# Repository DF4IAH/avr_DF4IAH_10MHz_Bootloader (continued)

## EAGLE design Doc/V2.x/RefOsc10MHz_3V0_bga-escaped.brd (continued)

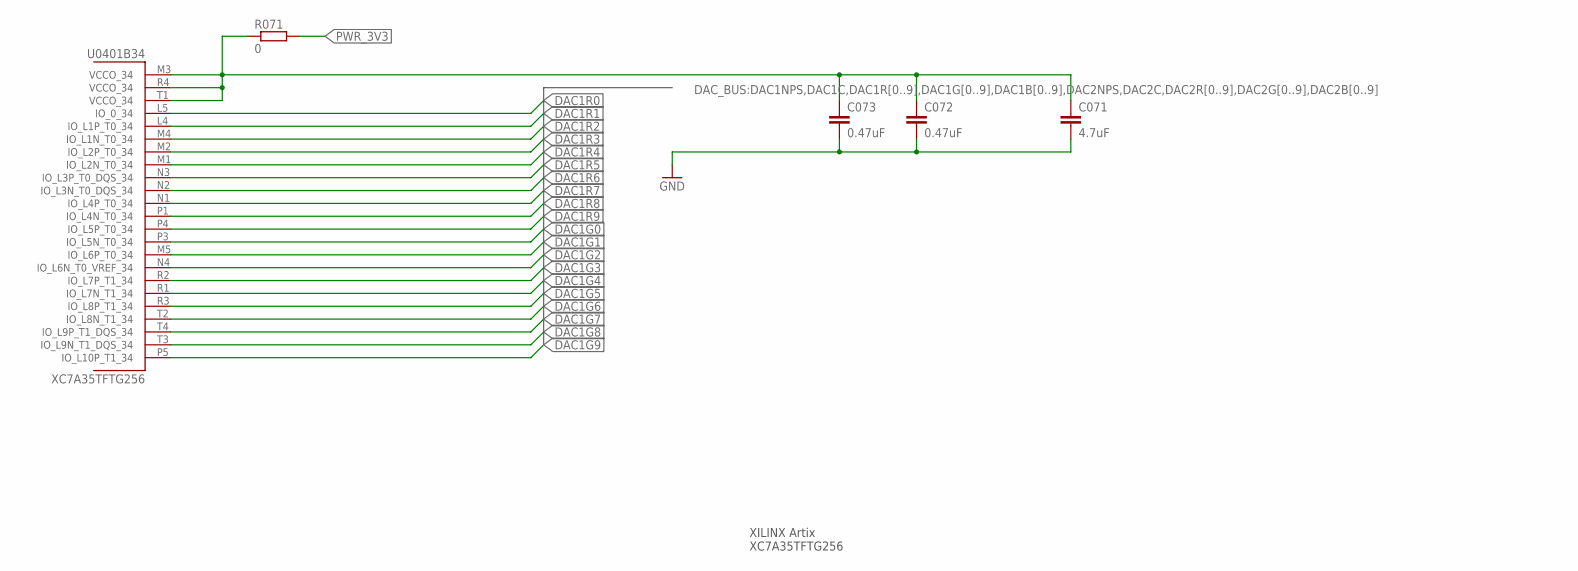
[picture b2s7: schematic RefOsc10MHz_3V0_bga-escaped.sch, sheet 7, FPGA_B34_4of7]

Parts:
C071: 4.7uF; C0402
C072, C073: 0.47uF; C0402
R071: 0; R0402
U0401: XC7A35TFTG256; FTG256_0MM4

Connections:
DAC1G0: U0401.P3 (IO_L5N_T0_34)
DAC1G1: U0401.M5 (IO_L6P_T0_34)
DAC1G2: U0401.N4 (IO_L6N_T0_VREF_34)
DAC1G3: U0401.R2 (IO_L7P_T1_34)
DAC1G4: U0401.R1 (IO_L7N_T1_34)
DAC1G5: U0401.R3 (IO_L8P_T1_34)
DAC1G6: U0401.T2 (IO_L8N_T1_34)
DAC1G7: U0401.T4 (IO_L9P_T1_DQS_34)
DAC1G8: U0401.T3 (IO_L9N_T1_DQS_34)
DAC1G9: U0401.P5 (IO_L10P_T1_34)
DAC1R0: U0401.L5 (IO_0_34)
DAC1R1: U0401.L4 (IO_L1P_T0_34)
DAC1R2: U0401.M4 (IO_L1N_T0_34)
DAC1R3: U0401.M2 (IO_L2P_T0_34)
DAC1R4: U0401.M1 (IO_L2N_T0_34)
DAC1R5: U0401.N3 (IO_L3P_T0_DQS_34)
DAC1R6: U0401.N2 (IO_L3N_T0_DQS_34)
DAC1R7: U0401.N1 (IO_L4P_T0_34)
DAC1R8: U0401.P1 (IO_L4N_T0_34)
DAC1R9: U0401.P4 (IO_L5P_T0_34)
FPGA_VCCO_34: C071.1, C072.1, C073.1, R071.1, U0401.M3 (VCCO_34), U0401.R4 (VCCO_34), U0401.T1 (VCCO_34)
GND: C071.2, C072.2, C073.2; also elsewhere on the board
PWR_3V3: R071.2; also elsewhere on the board

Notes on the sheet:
XILINX Artix XC7A35TFTG256

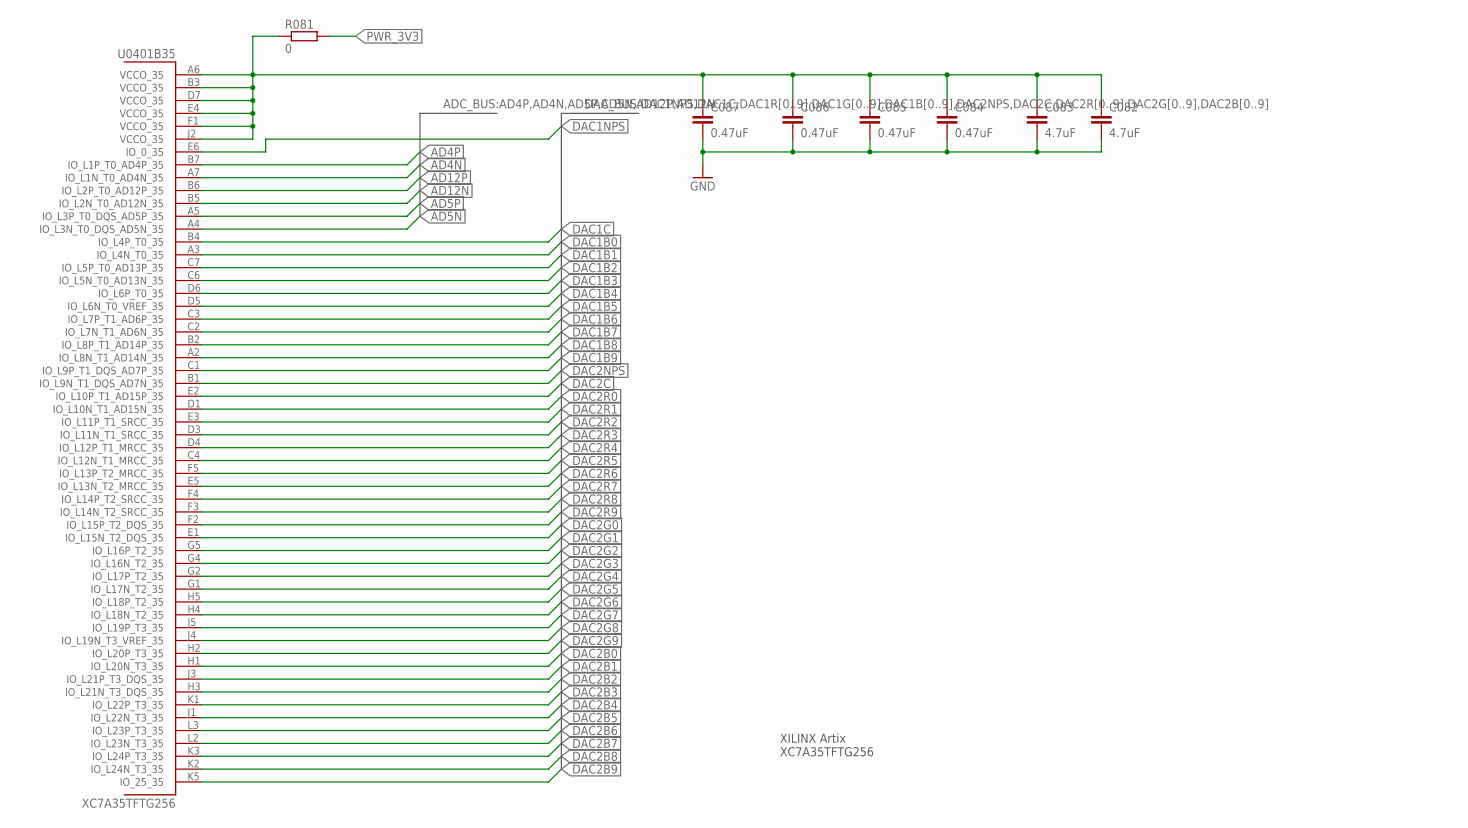
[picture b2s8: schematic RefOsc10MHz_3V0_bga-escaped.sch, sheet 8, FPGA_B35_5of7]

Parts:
C082, C083: 4.7uF; C0402
C084, C085, C086, C087: 0.47uF; C0402
R081: 0; R0402
U0401: XC7A35TFTG256; FTG256_0MM4

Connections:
AD4N: U0401.A7 (IO_L1N_T0_AD4N_35)
AD4P: U0401.B7 (IO_L1P_T0_AD4P_35)
AD5N: U0401.A4 (IO_L3N_T0_DQS_AD5N_35)
AD5P: U0401.A5 (IO_L3P_T0_DQS_AD5P_35)
AD12N: U0401.B5 (IO_L2N_T0_AD12N_35)
AD12P: U0401.B6 (IO_L2P_T0_AD12P_35)
DAC1B0: U0401.A3 (IO_L4N_T0_35)
DAC1B1: U0401.C7 (IO_L5P_T0_AD13P_35)
DAC1B2: U0401.C6 (IO_L5N_T0_AD13N_35)
DAC1B3: U0401.D6 (IO_L6P_T0_35)
DAC1B4: U0401.D5 (IO_L6N_T0_VREF_35)
DAC1B5: U0401.C3 (IO_L7P_T1_AD6P_35)
DAC1B6: U0401.C2 (IO_L7N_T1_AD6N_35)
DAC1B7: U0401.B2 (IO_L8P_T1_AD14P_35)
DAC1B8: U0401.A2 (IO_L8N_T1_AD14N_35)
DAC1B9: U0401.C1 (IO_L9P_T1_DQS_AD7P_35)
DAC1C: U0401.B4 (IO_L4P_T0_35)
DAC1NPS: U0401.E6 (IO_0_35)
DAC2B0: U0401.H1 (IO_L20N_T3_35)
DAC2B1: U0401.J3 (IO_L21P_T3_DQS_35)
DAC2B2: U0401.H3 (IO_L21N_T3_DQS_35)
DAC2B3: U0401.K1 (IO_L22P_T3_35)
DAC2B4: U0401.J1 (IO_L22N_T3_35)
DAC2B5: U0401.L3 (IO_L23P_T3_35)
DAC2B6: U0401.L2 (IO_L23N_T3_35)
DAC2B7: U0401.K3 (IO_L24P_T3_35)
DAC2B8: U0401.K2 (IO_L24N_T3_35)
DAC2B9: U0401.K5 (IO_25_35)
DAC2C: U0401.E2 (IO_L10P_T1_AD15P_35)
DAC2G0: U0401.E1 (IO_L15N_T2_DQS_35)
DAC2G1: U0401.G5 (IO_L16P_T2_35)
DAC2G2: U0401.G4 (IO_L16N_T2_35)
DAC2G3: U0401.G2 (IO_L17P_T2_35)
DAC2G4: U0401.G1 (IO_L17N_T2_35)
DAC2G5: U0401.H5 (IO_L18P_T2_35)
DAC2G6: U0401.H4 (IO_L18N_T2_35)
DAC2G7: U0401.J5 (IO_L19P_T3_35)
DAC2G8: U0401.J4 (IO_L19N_T3_VREF_35)
DAC2G9: U0401.H2 (IO_L20P_T3_35)
DAC2NPS: U0401.B1 (IO_L9N_T1_DQS_AD7N_35)
DAC2R0: U0401.D1 (IO_L10N_T1_AD15N_35)
DAC2R1: U0401.E3 (IO_L11P_T1_SRCC_35)
DAC2R2: U0401.D3 (IO_L11N_T1_SRCC_35)
DAC2R3: U0401.D4 (IO_L12P_T1_MRCC_35)
DAC2R4: U0401.C4 (IO_L12N_T1_MRCC_35)
DAC2R5: U0401.F5 (IO_L13P_T2_MRCC_35)
DAC2R6: U0401.E5 (IO_L13N_T2_MRCC_35)
DAC2R7: U0401.F4 (IO_L14P_T2_SRCC_35)
DAC2R8: U0401.F3 (IO_L14N_T2_SRCC_35)
DAC2R9: U0401.F2 (IO_L15P_T2_DQS_35)
FPGA_VCCO_35: C082.1, C083.1, C084.1, C085.1, C086.1, C087.1, R081.1, U0401.A6 (VCCO_35), U0401.B3 (VCCO_35), U0401.D7 (VCCO_35), U0401.E4 (VCCO_35), U0401.F1 (VCCO_35), U0401.J2 (VCCO_35)
GND: C082.2, C083.2, C084.2, C085.2, C086.2, C087.2; also elsewhere on the board
PWR_3V3: R081.2; also elsewhere on the board

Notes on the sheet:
XILINX Artix XC7A35TFTG256

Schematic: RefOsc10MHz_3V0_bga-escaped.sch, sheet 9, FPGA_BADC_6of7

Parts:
C091: 4.7uF; C0402
C092: 0.47uF; C0402
R091: 0; R0402
U0401: XC7A35TFTG256; FTG256_0MM4

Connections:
AGND: U0401.G7 (GNDADC_0), U0401.H7 (VREFN_0), U0401.J7 (VN_0); also elsewhere on the board
FPGA_ADC_VP_0: U0401.H8 (VP_0)
FPGA_VCCADC_0: C091.1, C092.1, R091.1, U0401.G8 (VCCADC_0)
GND: C091.2, C092.2; also elsewhere on the board
PWR_1V25_PREC: U0401.J8 (VREFP_0)
PWR_VCCADC: R091.2; also elsewhere on the board

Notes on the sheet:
XILINX Artix XC7A35TFTG256

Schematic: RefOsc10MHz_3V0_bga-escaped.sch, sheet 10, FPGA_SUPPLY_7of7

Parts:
C1001: 100uF; C1206
C1002, C1003, C1022, C1023: 4.7uF; C0402
C1004, C1005, C1006, C1012, C1024, C1025, C1026: 0.47uF; C0402
C1011, C1021: 47uF; C0805
R101, R102, R103, R104, R105: 0; R0402
U0401: XC7A35TFTG256; FTG256_0MM4

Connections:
FPGA_DXN_0: R105.1, U0401.K7 (DXN_0)
FPGA_DXP_0: R104.1, U0401.K8 (DXP_0)
FPGA_VCCAUX: C1021.1, C1022.1, C1023.1, C1024.1, C1025.1, C1026.1, R103.1, U0401.G10 (VCCAUX), U0401.J10 (VCCAUX), U0401.K11 (VCCAUX), U0401.L10 (VCCAUX)
FPGA_VCCBRAM: C1011.1, C1012.1, R102.1, U0401.E10 (VCCBRAM), U0401.F11 (VCCBRAM)
FPGA_VCCINT: C1001.1, C1002.1, C1003.1, C1004.1, C1005.1, C1006.1, R101.1, U0401.F7 (VCCINT), U0401.F9 (VCCINT), U0401.G6 (VCCINT), U0401.H9 (VCCINT), U0401.J6 (VCCINT), U0401.K9 (VCCINT), U0401.L8 (VCCINT)
GND: C1001.2, C1002.2, C1003.2, C1004.2, C1005.2, C1006.2, C1011.2, C1012.2, C1021.2, C1022.2, C1023.2, C1024.2, C1025.2, C1026.2, R104.2, R105.2, U0401.A1 (GND), U0401.A11 (GND), U0401.B8 (GND), U0401.C5 (GND), U0401.C15 (GND), U0401.D2 (GND), U0401.D12 (GND), U0401.E9 (GND), U0401.F6 (GND), U0401.F10 (GND), U0401.F16 (GND), U0401.G3 (GND), U0401.G9 (GND), U0401.G13 (GND), U0401.H6 (GND), U0401.J9 (GND), U0401.J11 (GND), U0401.K4 (GND), U0401.K6 (GND), U0401.K14 (GND), U0401.L1 (GND), U0401.L11 (GND), U0401.M8 (GND), U0401.N5 (GND), U0401.N15 (GND), U0401.P2 (GND), U0401.P12 (GND), U0401.R9 (GND), U0401.T6 (GND), U0401.T16 (GND); also elsewhere on the board
PWR_1V0: R101.2, R102.2; also elsewhere on the board
PWR_1V8: R103.2; also elsewhere on the board

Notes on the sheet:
XILINX Artix XC7A35TFTG256

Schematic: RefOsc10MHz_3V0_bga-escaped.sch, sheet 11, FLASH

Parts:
R111: 4.7k; R0805
R112, R113: 100k; R0805
U111: N25Q128A13ESE40F; SOP2-8

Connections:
FPGA_SPI_CCLK: U111.6 (C); also elsewhere on the board
FPGA_SPI_D00_MOSI: U111.5 (DQ0); also elsewhere on the board
FPGA_SPI_D01_DIN: U111.2 (DQ1); also elsewhere on the board
FPGA_SPI_D02: R112.1, U111.3 (W#_VPP_DQ2); also elsewhere on the board
FPGA_SPI_D03: R113.1, U111.7 (HOLD#/DQ3); also elsewhere on the board
FPGA_SPI_FCS_B#: R111.1, U111.1 (S#); also elsewhere on the board
GND: U111.4 (VSS); also elsewhere on the board
PWR_3V3: R111.2, R112.2, R113.2, U111.8 (VDD); also elsewhere on the board

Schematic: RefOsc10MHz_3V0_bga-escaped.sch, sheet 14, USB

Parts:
C141: 47uF; C0805
C142: 100n; C0805
CON141: TYCO-AMP_USBUSB-B_SMT; TYCO-AMP_USB-B_SMT
D141, D142: BZX84-C3V6; TO236
R141, R142: 68; R0805
R143: 1M; R0805
R144: 1.5k; R0805
RP141: 1206L025YR_0.5A; M1206

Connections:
GND: C141.2, C142.2, CON141.4 (GND), D141.A, D142.A, R143.1; also elsewhere on the board
PWR_5V0: C141.1, C142.1, RP141.2; also elsewhere on the board
USB_DISC: R144.2; also elsewhere on the board
USB_D_MIN1: CON141.2 (D-), D142.C, R142.1, R144.1
USB_D_MNS: R142.2; also elsewhere on the board
USB_D_PLS: R141.2; also elsewhere on the board
USB_D_PLS1: CON141.3 (D+), D141.C, R141.1, R143.2
USB_PWR1: CON141.1 (VBUS), RP141.1

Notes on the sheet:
USB-B

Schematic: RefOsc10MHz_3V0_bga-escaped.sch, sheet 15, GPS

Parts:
C151: 100n; C0805
CON151: HEADER-2X5SMD; 2X5SMD
LP151: WE-CBF_300R; L3216C
R151, R152: 100k; R0805
RP151: 1206L012WR_0.1A; M1206
U151: TJ1513MTBD

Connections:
GND: C151.2, CON151.1, CON151.9, CON151.10, U151.6 (GND), U151.17 (GND), U151.20 (GND), U151.22 (GND); also elsewhere on the board
GPS_ANT: LP151.1, U151.21 (RF_IN); also elsewhere on the board
GPS_NMEA_RX: CON151.5, R152.1, U151.5 (RXD1); also elsewhere on the board
GPS_NMEA_TX: CON151.6, U151.4 (TXD1); also elsewhere on the board
GPS_PPS: CON151.7, U151.3 (TIMEPULSE); also elsewhere on the board
GPS_PWR_3V3: C151.1, CON151.4, R151.2, R152.2, RP151.2, U151.13 (VCC)
GPS_RESET: R151.1, U151.11 (RESET); also elsewhere on the board
unnamed: LP151.2, U151.19 (VCC_RF)
PWR_3V3: RP151.1; also elsewhere on the board
PWR_5V0: CON151.3; also elsewhere on the board
PWR_BACKUP_3V3: CON151.2, U151.12 (V_BAKP); also elsewhere on the board

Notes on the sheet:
GPS - PINs: 1 GND 2 V_BAT, Memory Supply, Goldcap 3 VCC 5V 4 V_ANT 5V, fused 5 GPS NMEA RX 6 GPS NMEA TX 7 PPS (1 Hz) 8 Ref. 10 kHz 9 GND 10 GND

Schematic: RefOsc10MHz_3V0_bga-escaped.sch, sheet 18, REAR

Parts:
CON181, CON183, CON184, CON185, CON186: MCX-J-P-X-RA-SM1
CON182: SD-73100-0105; MOLEX_BNC-JACK-50R_SD-73100-0105
R181: 51; R0805
R182, R183: 120; R0805
U181: OPA357; SOT-23-6

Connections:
GND: CON181.2, CON181.3, CON181.4, CON181.5, CON182.2, CON182.3, CON183.2, CON183.3, CON183.4, CON183.5, CON184.2, CON184.3, CON184.4, CON184.5, CON185.2, CON185.3, CON185.4, CON185.5, CON186.2, CON186.3, CON186.4, CON186.5, R182.1, R183.1, U181.2 (V-); also elsewhere on the board
GPS_ANT: CON181.1; also elsewhere on the board
unnamed: R181.1, U181.1 (OUT)
unnamed: CON182.1, R181.2
PWR_5V0: U181.6 (V+); also elsewhere on the board
REFC_10MHZ_EN: U181.5 (ENABLE); also elsewhere on the board
REFC_10MHZ_N: R183.2, U181.4 (-IN); also elsewhere on the board
REFC_10MHZ_P: R182.2, U181.3 (+IN); also elsewhere on the board
SIG_CH0_I: CON183.1
SIG_CH0_Q: CON184.1
SIG_CH1_I: CON185.1
SIG_CH1_Q: CON186.1

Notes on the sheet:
10 MHz RefClk Out
GPS Ant In
CH0 I Out
CH0 Q Out
CH1 I Out
CH1 Q Out

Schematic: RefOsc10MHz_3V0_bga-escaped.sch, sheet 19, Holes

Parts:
H191, H192, H193, H194: MOUNT-PAD-ROUND2.8; 2,8-PAD

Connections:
GND: H191.B2,8, H192.B2,8, H193.B2,8, H194.B2,8; also elsewhere on the board

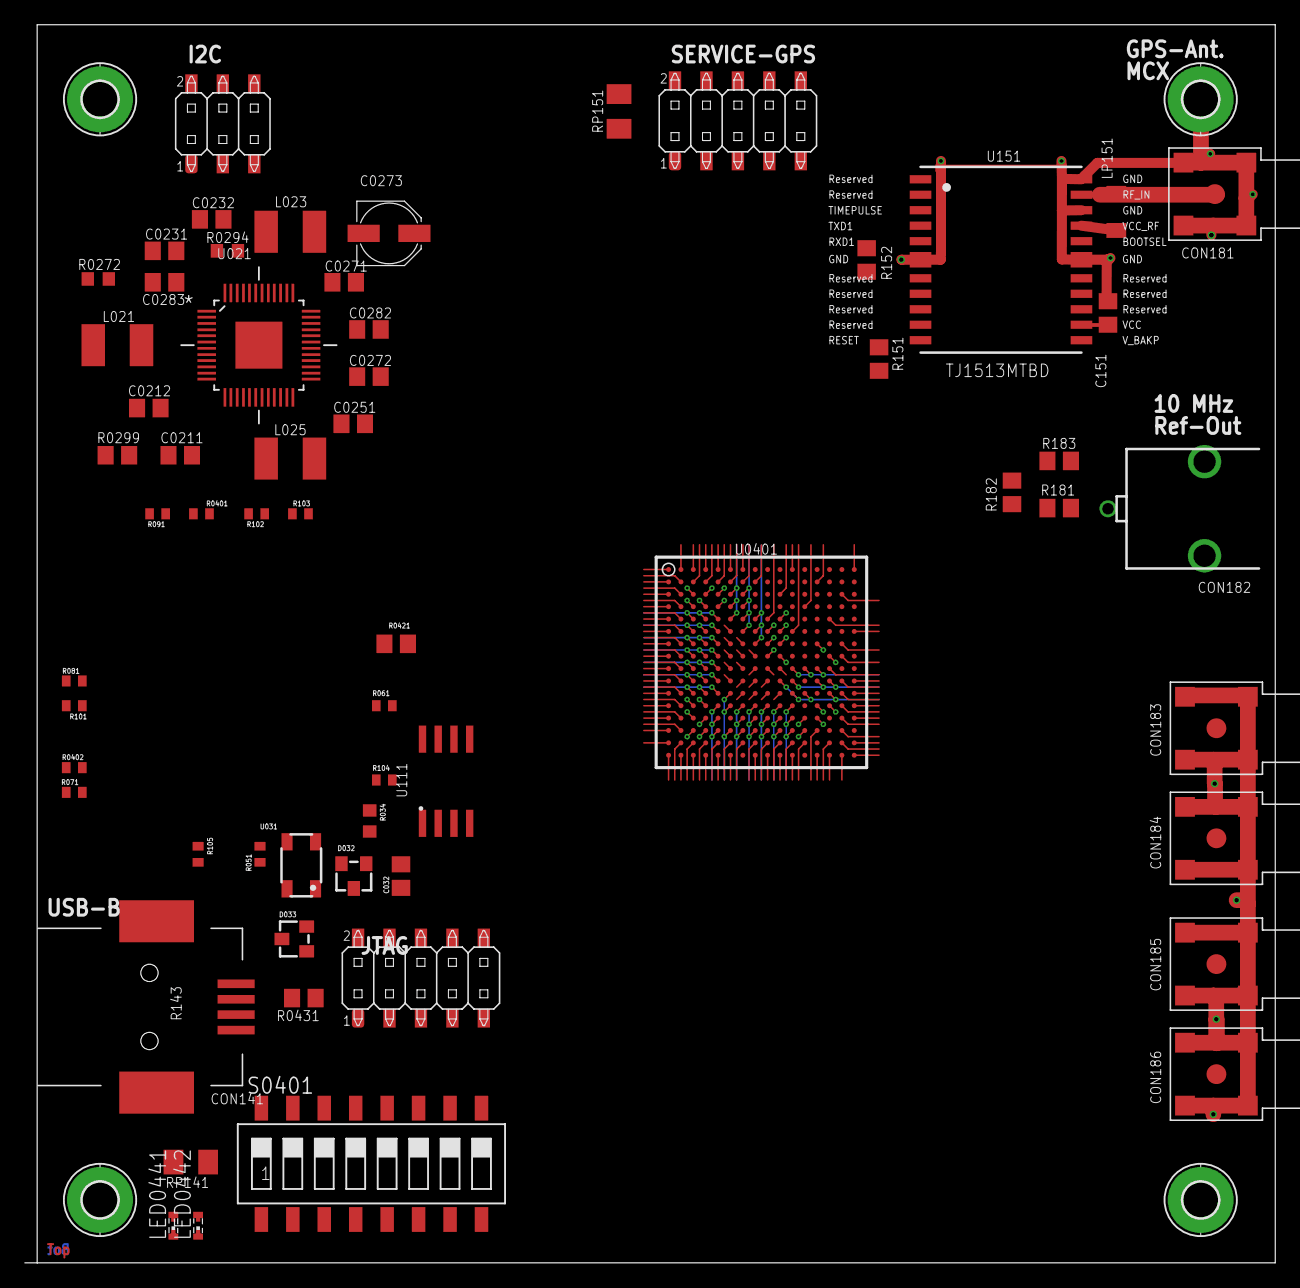
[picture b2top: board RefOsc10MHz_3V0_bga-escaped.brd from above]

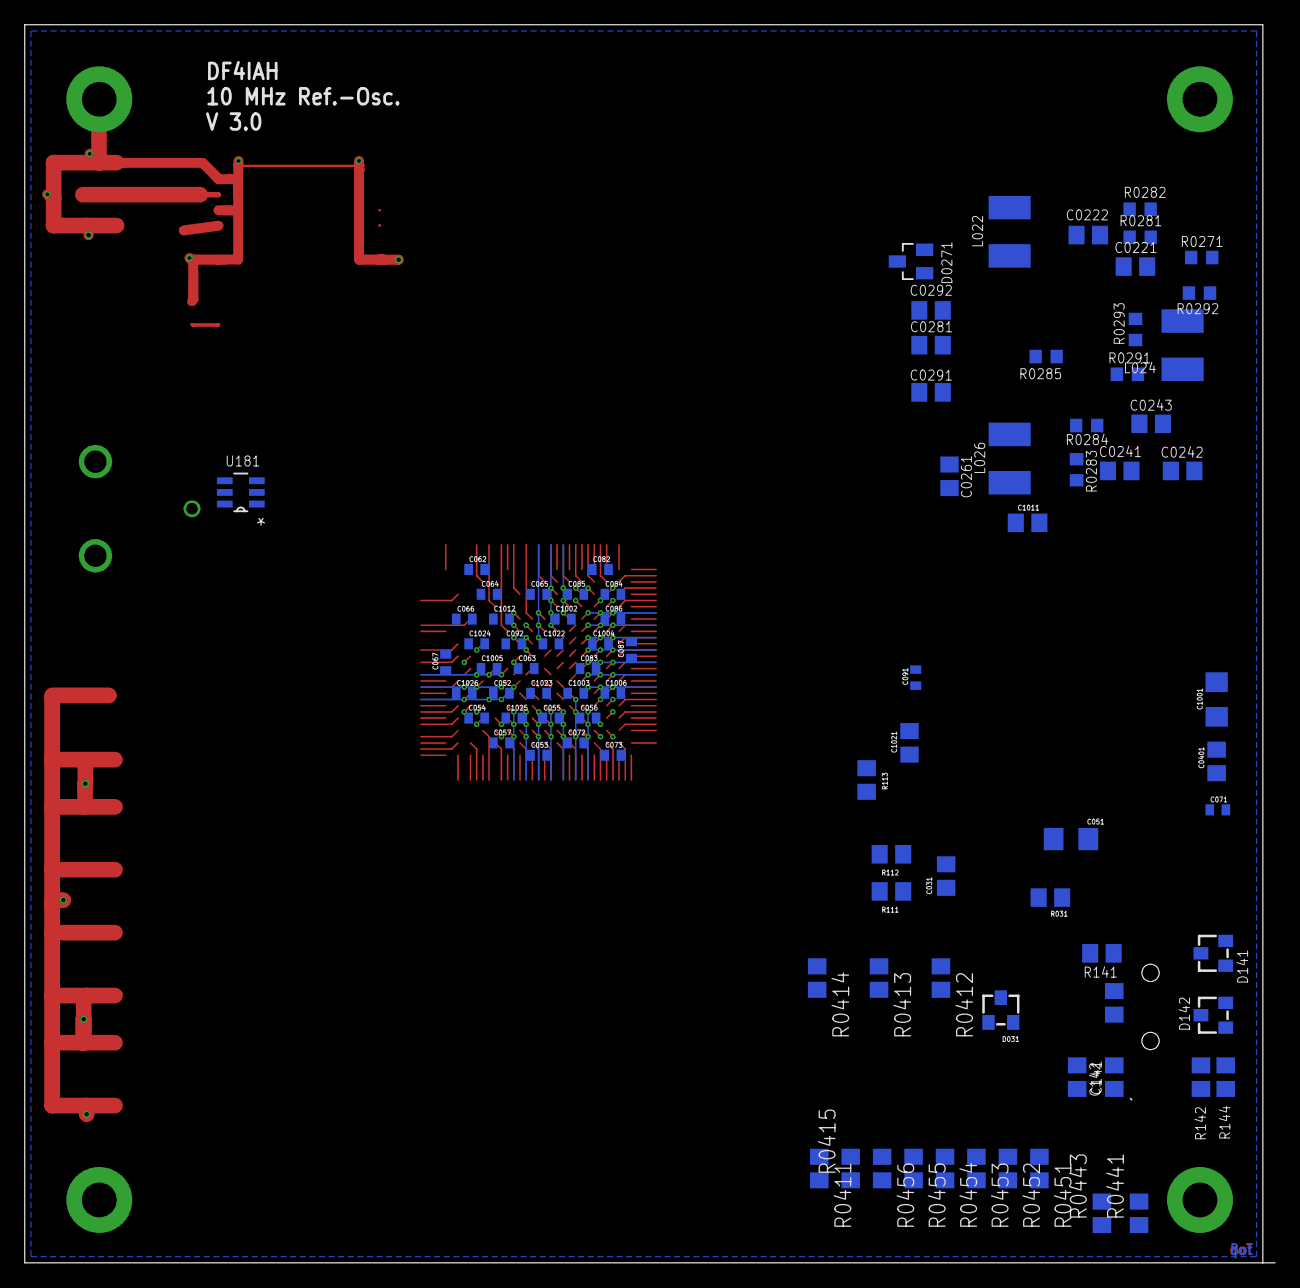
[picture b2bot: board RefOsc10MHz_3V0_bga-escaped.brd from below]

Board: 4 copper layers, 101.0 x 100.0 mm, 154 parts (89 on the bottom side), 94 nets.

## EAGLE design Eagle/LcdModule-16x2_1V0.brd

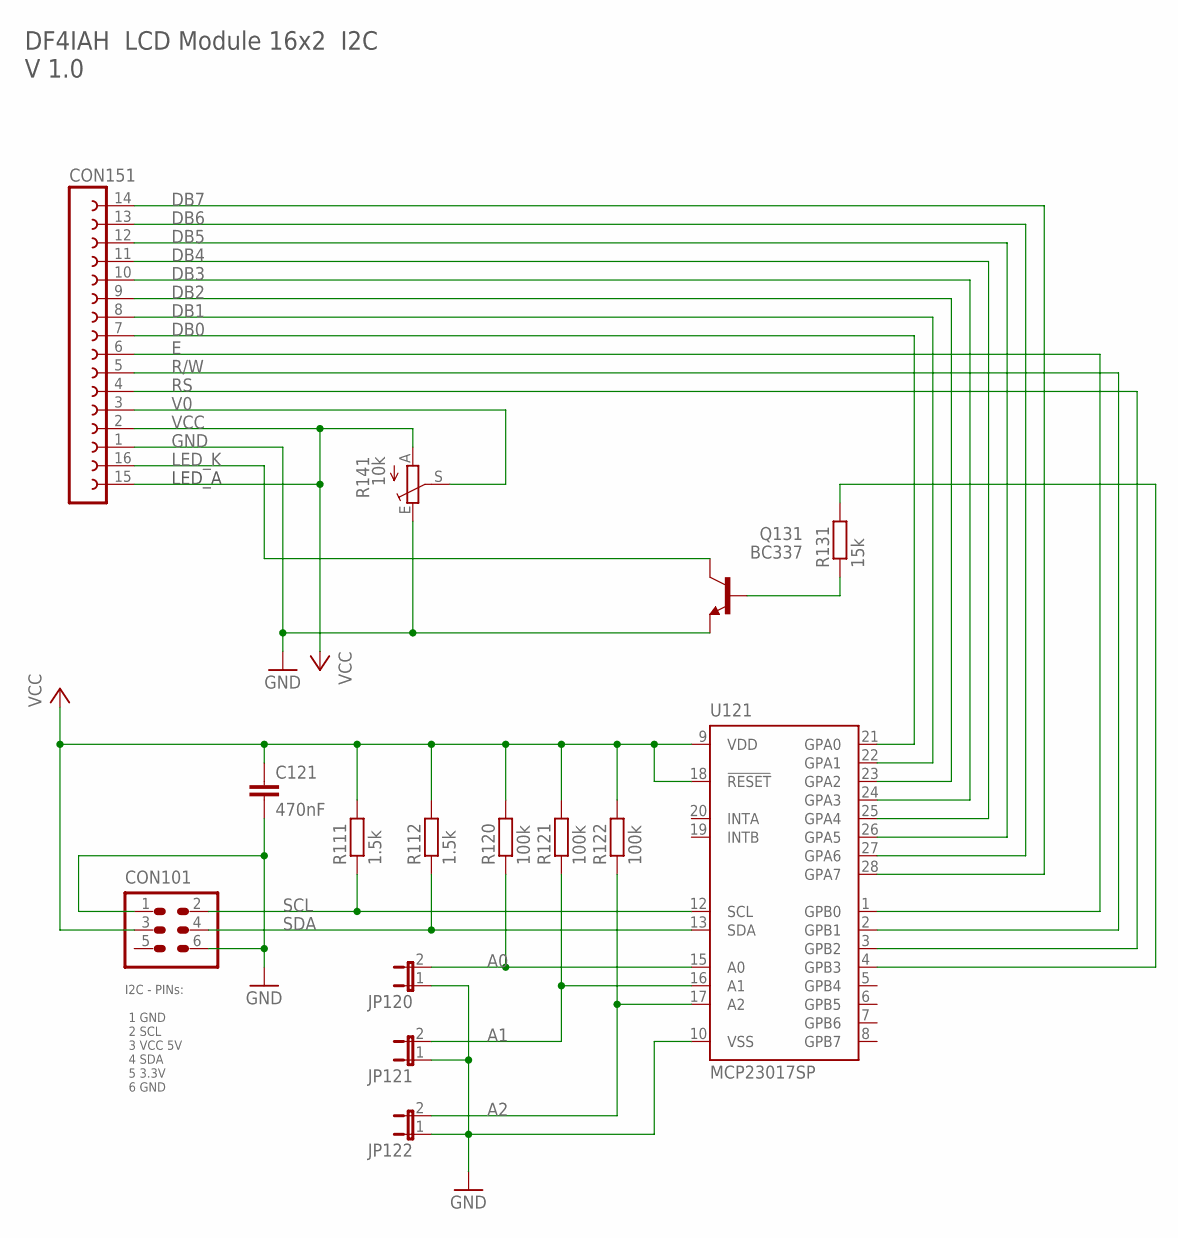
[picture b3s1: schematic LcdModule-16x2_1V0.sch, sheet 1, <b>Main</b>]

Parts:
C121: 470nF; C0805
CON101: HEADER-2X3SMD; 2X03SMD
CON151: CON_LCDBRD_16W
JP120, JP121, JP122: JP1E; JP1
Q131: BC337; TO92
R111, R112: 1.5k; R0805
R120, R121, R122: 100k; R0805
R131: 15k; R0805
R141: 10k; PT-10
U121: MCP23017SP; DIL28-3

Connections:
A0: JP120.2, R120.1, U121.15 (A0)
A1: JP121.2, R121.1, U121.16 (A1)
A2: JP122.2, R122.1, U121.17 (A2)
DB0: CON151.7, U121.21 (GPA0)
DB1: CON151.8, U121.22 (GPA1)
DB2: CON151.9, U121.23 (GPA2)
DB3: CON151.10, U121.24 (GPA3)
DB4: CON151.11, U121.25 (GPA4)
DB5: CON151.12, U121.26 (GPA5)
DB6: CON151.13, U121.27 (GPA6)
DB7: CON151.14, U121.28 (GPA7)
E: CON151.6, U121.1 (GPB0)
GND: C121.2, CON101.1, CON101.6, CON151.1, JP120.1, JP121.1, JP122.1, Q131.1 (E), R141.E, U121.10 (VSS); also elsewhere on the board
LED: R131.2, U121.4 (GPB3)
LED_K: CON151.16, Q131.3 (C)
unnamed: Q131.2 (B), R131.1
R/W: CON151.5, U121.2 (GPB1)
RS: CON151.4, U121.3 (GPB2)
SCL: CON101.2, R111.1, U121.12 (SCL)
SDA: CON101.4, R112.1, U121.13 (SDA)
V0: CON151.3, R141.S
VCC: C121.1, CON101.3, CON151.2, CON151.15, R111.2, R112.2, R120.2, R121.2, R122.2, R141.A, U121.9 (VDD), U121.18 (!RESET)

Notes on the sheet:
DF4IAH LCD Module 16x2 I2C V 1.0
I2C - PINs: 1 GND 2 SCL 3 VCC 5V 4 SDA 5 3.3V 6 GND
LED_A

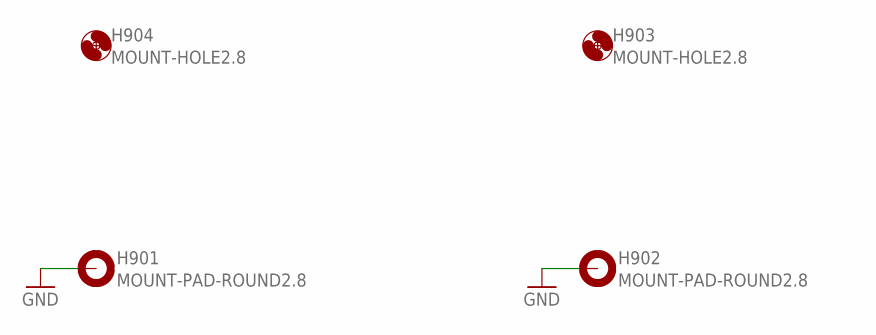
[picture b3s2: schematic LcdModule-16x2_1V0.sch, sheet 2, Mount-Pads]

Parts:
H901, H902: MOUNT-PAD-ROUND2.8; 2,8-PAD
H903, H904: MOUNT-HOLE2.8; 2,8

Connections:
GND: H901.B2,8, H902.B2,8; also elsewhere on the board

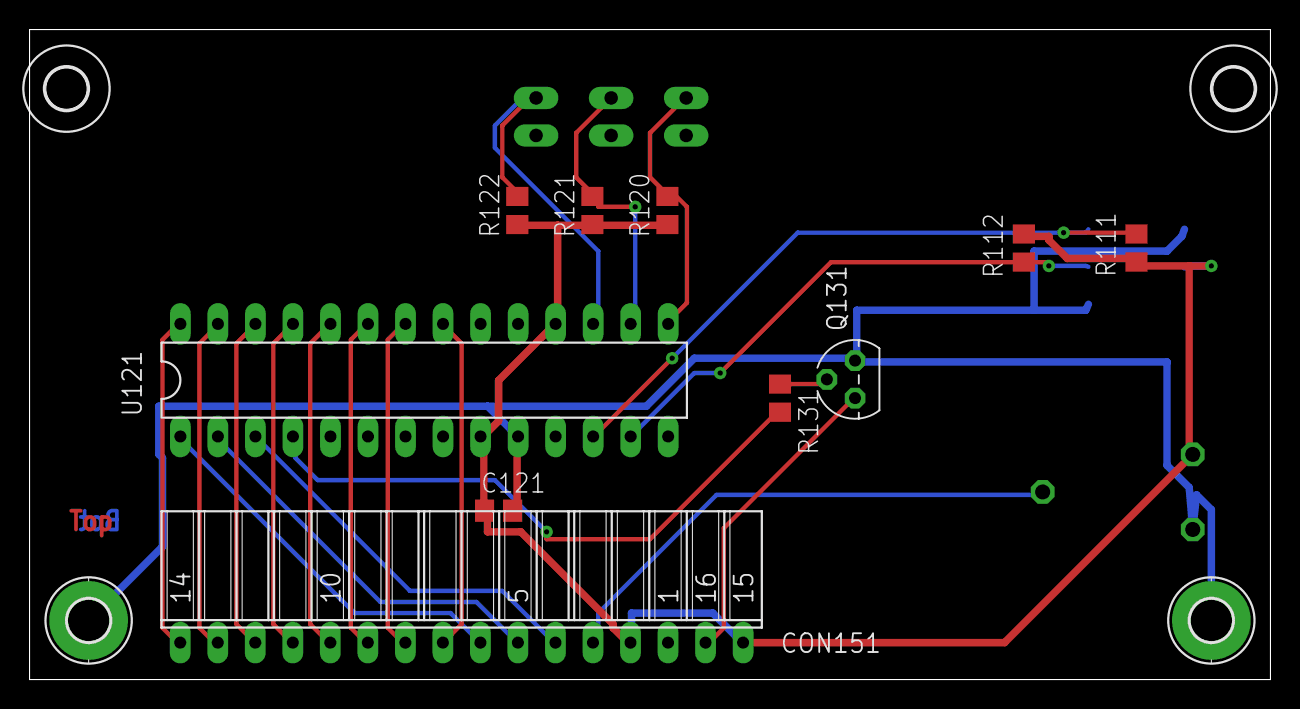
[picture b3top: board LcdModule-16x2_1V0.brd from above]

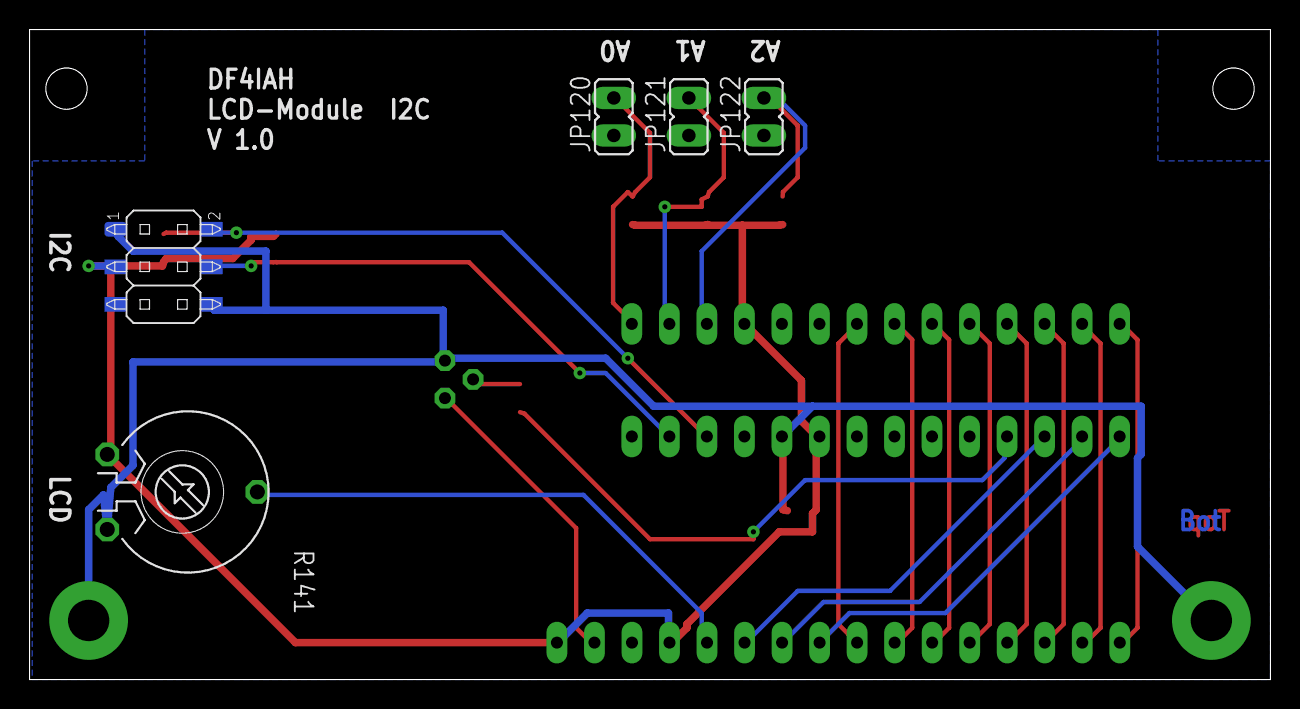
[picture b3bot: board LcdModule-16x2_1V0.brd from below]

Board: 2 copper layers, 84.0 x 44.0 mm, 19 parts (5 on the bottom side), 22 nets.

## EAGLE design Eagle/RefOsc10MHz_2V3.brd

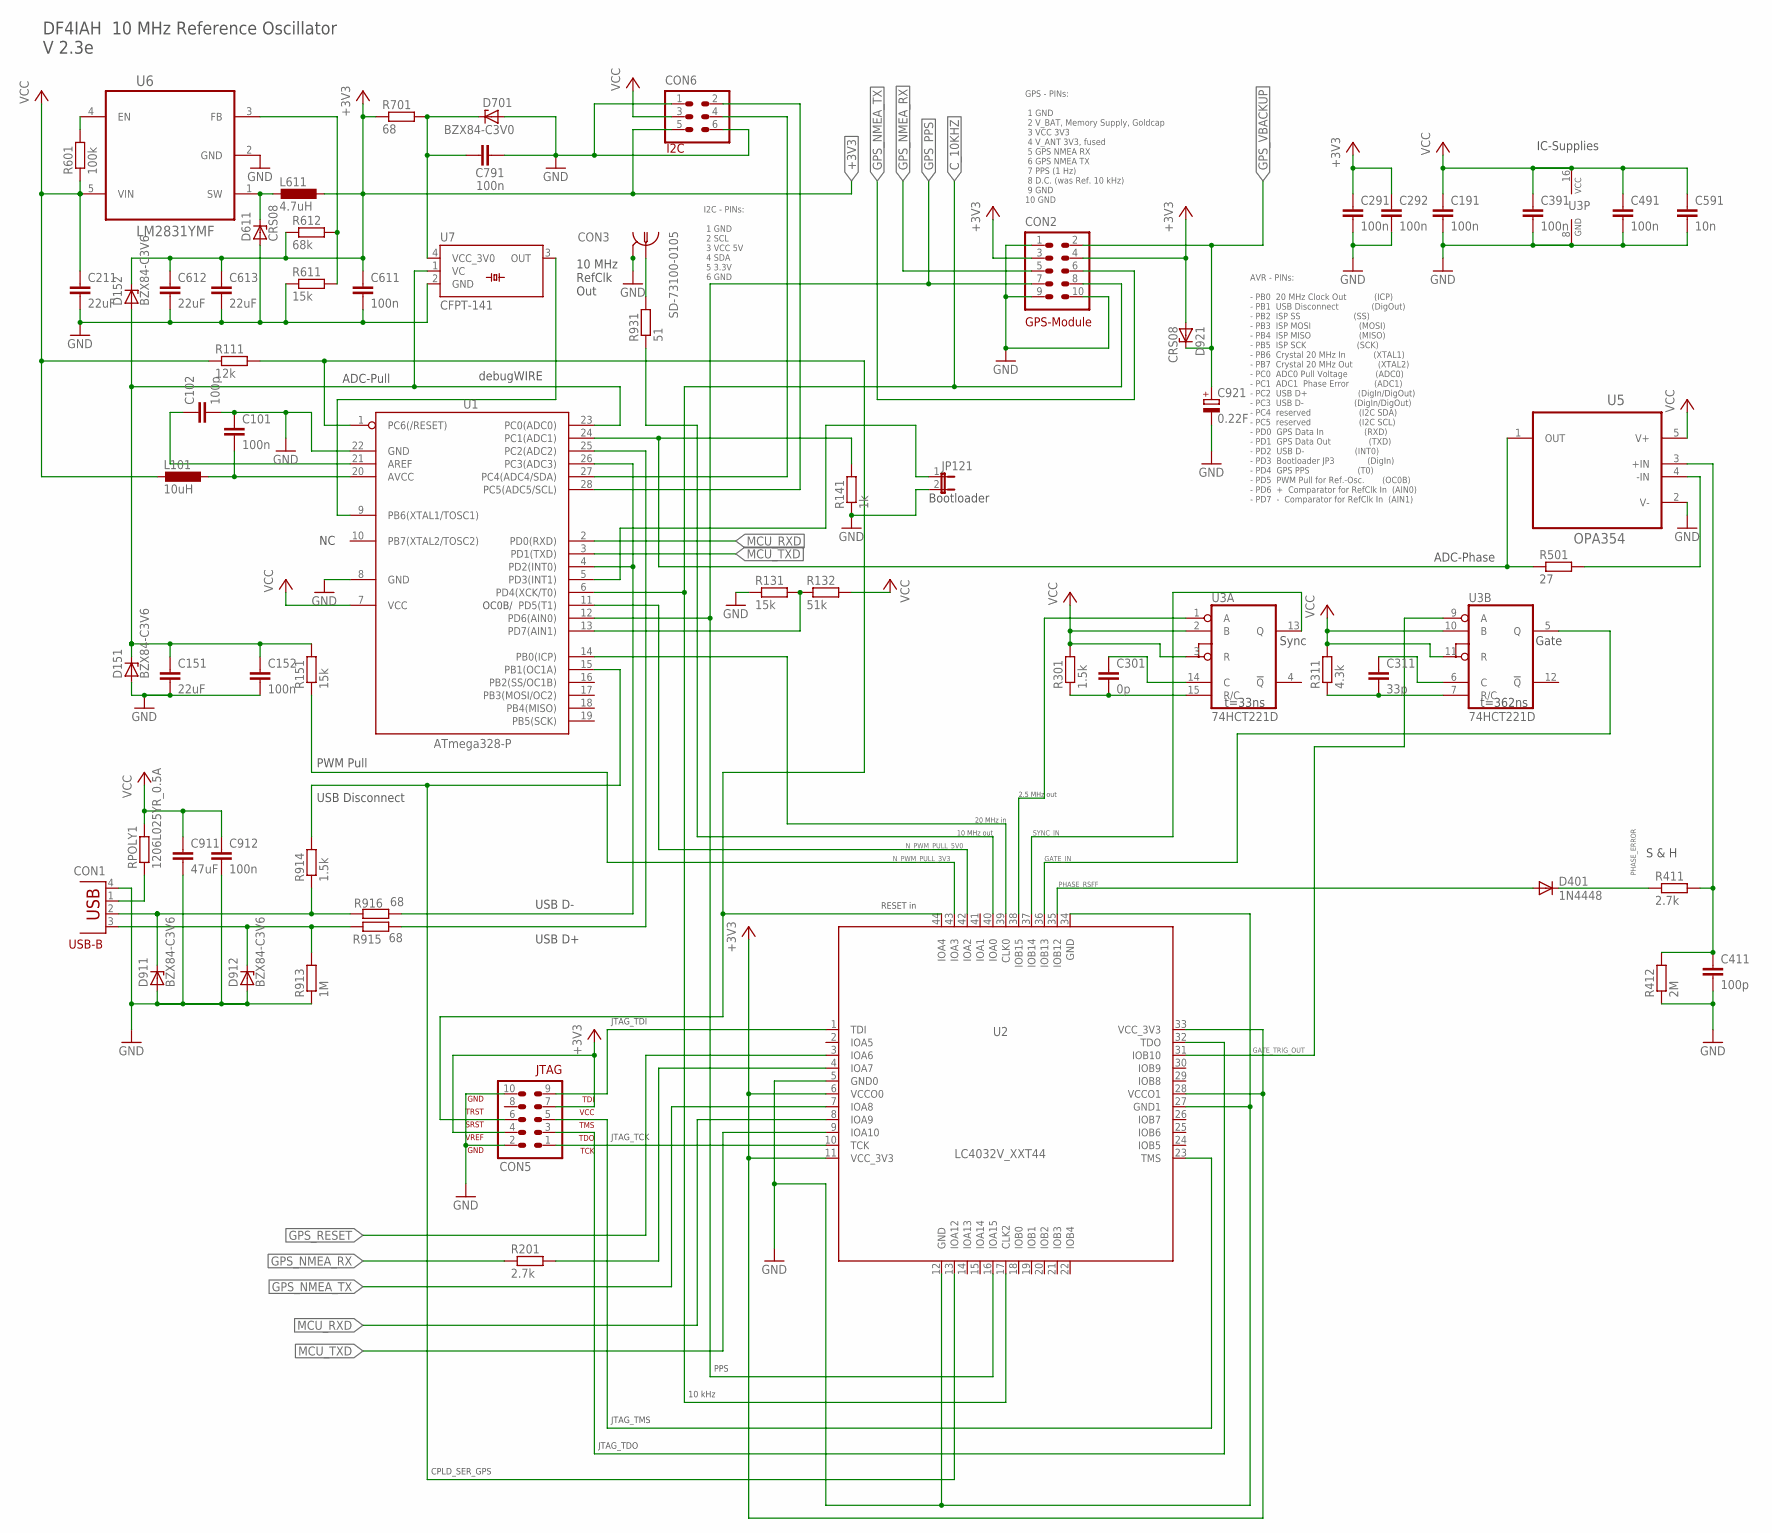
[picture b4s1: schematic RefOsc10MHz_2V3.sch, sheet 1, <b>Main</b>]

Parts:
C101, C152, C191, C291, C292, C391, C491, C611, C791, C912: 100n; C0805
C102, C411: 100p; C0805
C151, C211, C612, C613: 22uF; C0805
C301: 0p; C0805
C311: 33p; C0805
C591: 10n; C0805
C911: 47uF; C0805
C921: 0.22F; 140CLH-1010
CON1: TYCO-AMP_USBUSB-B_SMT; TYCO-AMP_USB-B_SMT
CON2: HEADER-2X5; 2X05
CON3: SD-73100-0105; MOLEX_BNC-JACK-50R_SD-73100-0105
CON5: AVR-JTAG-10
CON6: HEADER-2X3; 2X03
D151, D152, D911, D912: BZX84-C3V6; TO236
D401: 1N4448; DO35-7
D611, D921: CRS08; SOD80C
D701: BZX84-C3V0; TO236
JP121: JP1E; JP1
L101: 10uH; L1812
L611: 4.7uH; L5650M
R111: 12k; R0805
R131, R151, R611: 15k; R0805
R132: 51k; R0805
R141: 1k; R0805
R201, R411: 2.7k; R0805
R301, R914: 1.5k; R0805
R311: 4.3k; R0805
R412: 2M; R0805
R501: 27; R0805
R601: 100k; R0805
R612: 68k; R0805
R701, R915, R916: 68; R0805
R913: 1M; R0805
R931: 51; R0805
RPOLY1: 1206L025YR_0.5A; M1206
U1: ATmega328-P; DIL28-3
U2: LC4032V_XXT44; TQFP44
U3: 74HCT221D; SO16
U5: OPA354; SOT-23-5
U6: LM2831YMF; SOT95P280X145-5N
U7: CFPT-141

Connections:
+3V0: C791.1, D701.C, R701.2, U7.4 (VCC_3V0)
+3V3: C291.1, C292.1, C611.1, C612.1, C613.1, CON2.3, CON2.4, CON5.4, CON5.7, CON6.5, D152.C, D921.A, L611.1, R612.1, R701.1, U2.6 (VCCO0), U2.11 (VCC_3V3), U2.28 (VCCO1), U2.33 (VCC_3V3); also elsewhere on the board
ADC_PHASE: R141.2, R501.1, U1.24 (PC1(ADC1)), U5.1 (OUT)
ADC_PHASE_SAMPLEHOLD: C411.1, R411.2, R412.2, U5.3 (+IN)
AIN1: R131.2, R132.1, U1.13 (PD7(AIN1))
AREF: C102.1, U1.21 (AREF)
AVCC: C101.2, L101.1, U1.20 (AVCC)
CPLD_GPS_NMEA_RX: R201.2, U2.4 (IOA7)
C_2MHZ5: U2.38 (IOB15), U3.1 (A)
C_10KHZ: CON2.8, U1.6 (PD4(XCK/T0)), U2.17 (CLK2)
C_10MHZ: CON3.1, R931.2
C_20MHZ: U1.14 (PB0(ICP)), U2.39 (CLK0)
D_10MHZ: R931.1, U2.40 (IOA0)
EN: R601.2, U6.4 (EN)
FB: R611.2, R612.2, U6.3 (FB)
GATE_IN: U2.36 (IOB13), U3.5 (Q)
GATE_TRIG_OUT: U2.31 (IOB10), U3.9 (A)
GND: C101.1, C102.2, C151.2, C152.2, C191.2, C211.2, C291.2, C292.2, C391.2, C411.2, C491.2, C591.2, C611.2, C612.2, C613.2, C791.2, C911.2, C912.2, C921.-, CON1.4 (GND), CON2.1, CON2.9, CON2.10, CON3.2, CON3.3, CON5.2, CON5.10, CON6.1, CON6.6, D151.A, D611.A, D701.A, D911.A, D912.A, JP121.2, R131.1, R141.1, R412.1, R611.1, R913.1, U1.8 (GND), U1.22 (GND), U2.5 (GND0), U2.12 (GND), U2.27 (GND1), U2.34 (GND), U3.8 (GND), U5.2 (V-), U6.2 (GND), U7.2 (GND); also elsewhere on the board
GPS_NMEA_RX: CON2.5, R201.1; also elsewhere on the board
GPS_NMEA_TX: CON2.6, U2.7 (IOA8); also elsewhere on the board
GPS_PPS: CON2.7, U1.12 (PD6(AIN0)), U2.16 (IOA15); also elsewhere on the board
GPS_RESET: U2.3 (IOA6); also elsewhere on the board
GPS_VBACKUP: C921.+, CON2.2, D921.C; also elsewhere on the board
INT1: JP121.1, U1.5 (PD3(INT1))
JTAG_TCK: CON5.1, U2.10 (TCK)
JTAG_TDI: CON5.9, U2.1 (TDI)
JTAG_TDO: CON5.3, U2.32 (TDO)
JTAG_TMS: CON5.5, U2.23 (TMS)
MCU_RXD: U1.2 (PD0(RXD)), U2.8 (IOA9)
MCU_TXD: U1.3 (PD1(TXD)), U2.9 (IOA10)
unnamed: CON6.2, U1.28 (PC5(ADC5/SCL))
unnamed: CON6.4, U1.27 (PC4(ADC4/SDA))
unnamed: C311.2, R311.1, U3.7 (R/C)
unnamed: C311.1, U3.6 (C)
unnamed: C301.2, R301.1, U3.15 (R/C)
unnamed: C301.1, U3.14 (C)
N_ADC_PULL: C151.1, C152.1, D151.C, D152.A, R151.2, U1.23 (PC0(ADC0)), U7.1 (VC)
N_PWM_PULL_3V3: R151.1, U2.43 (IOA3)
N_PWM_PULL_5V0: U1.11 (PD5(T1)), U2.42 (IOA2)
N_USB_DISC: R914.2, U1.15 (PB1(OC1A)), U2.13 (IOA12)
N_USB_DMNS: R916.2, U1.4 (PD2(INT0)), U1.26 (PC3(ADC3))
N_USB_DPLS: R915.2, U1.25 (PC2(ADC2))
PHASE_ERROR: D401.C, R411.1
PHASE_RSFF: D401.A, U2.35 (IOB12)
RESET: CON5.6, R111.2, U1.1 (PC6(/RESET)), U2.44 (IOA4)
SW: D611.C, L611.2, U6.1 (SW)
SYNC_IN: U2.37 (IOB14), U3.13 (Q)
TOSC1: U1.9 (PB6(XTAL1/TOSC1)), U7.3 (OUT)
U5_FB: R501.2, U5.4 (-IN)
USB_D_MIN: CON1.2 (D-), D911.C, R914.1, R916.1
USB_D_PLS: CON1.3 (D+), D912.C, R913.2, R915.1
USB_PWR: CON1.1 (VBUS), RPOLY1.1
VCC: C191.1, C211.1, C391.1, C491.1, C591.1, C911.1, C912.1, CON6.3, L101.2, R111.1, R132.2, R301.2, R311.2, R601.1, RPOLY1.2, U1.7 (VCC), U3.2 (B), U3.3 (R), U3.10 (B), U3.11 (R), U3.16 (VCC), U5.5 (V+), U6.5 (VIN)

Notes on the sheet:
debugWIRE
USB-B
AVR - PINs: - PB0 20 MHz Clock Out (ICP) - PB1 USB Disconnect (DigOut) - PB2 ISP SS (SS) - PB3 ISP MOSI (MOSI) - PB4 ISP MISO (MISO) - PB5 ISP SCK (SCK) - PB6 Crystal 20 MHz In (XTAL1) - PB7 Crystal 20 MHz Out (XTAL2) - PC0 ADC0 Pull Voltage (ADC0) - PC1 ADC1 Phase Error (ADC1) - PC2 USB D+ (DigIn/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
10 MHz RefClk Out
Bootloader
Gate
GPS-Module
GPS - PINs: 1 GND 2 V_BAT, Memory Supply, Goldcap 3 VCC 3V3 4 V_ANT 3V3, fused 5 GPS NMEA RX 6 GPS NMEA TX 7 PPS (1 Hz) 8 D.C. (was Ref. 10 kHz) 9 GND 10 GND
S & H
ADC-Phase
PWM Pull
ADC-Pull
Sync
t=33ns
t=362ns
IC-Supplies
20 MHz in
10 MHz out
2.5 MHz out
DF4IAH 10 MHz Reference Oscillator V 2.3e
USB Disconnect
USB D-
USB D+
10 kHz
PPS
RESET in
JTAG_TMS
JTAG_TDO
JTAG_TCK
JTAG_TDI
CPLD_SER_GPS
I2C - PINs: 1 GND 2 SCL 3 VCC 5V 4 SDA 5 3.3V 6 GND
I2C
OC0B/

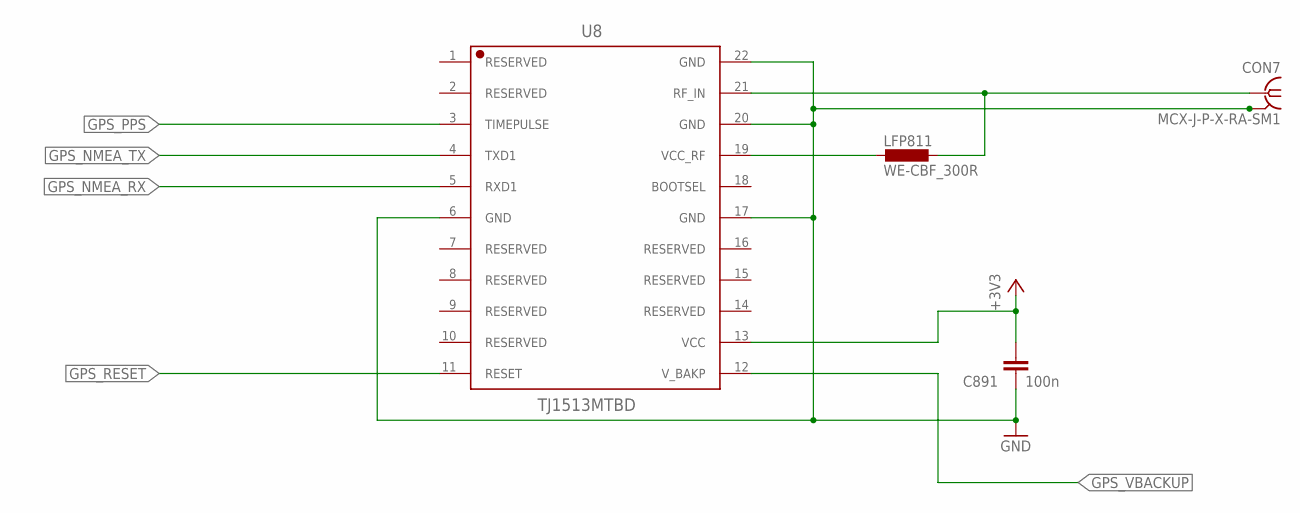
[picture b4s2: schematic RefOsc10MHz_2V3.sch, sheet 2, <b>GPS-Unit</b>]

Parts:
C891: 100n; C0805
CON7: MCX-J-P-X-RA-SM1
LFP811: WE-CBF_300R; L3216C
U8: TJ1513MTBD

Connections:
+3V3: C891.1, U8.13 (VCC); also elsewhere on the board
GND: C891.2, CON7.2, CON7.3, CON7.4, CON7.5, U8.6 (GND), U8.17 (GND), U8.20 (GND), U8.22 (GND); also elsewhere on the board
GPS_HF: CON7.1, LFP811.1, U8.21 (RF_IN)
GPS_NMEA_RX: U8.5 (RXD1); also elsewhere on the board
GPS_NMEA_TX: U8.4 (TXD1); also elsewhere on the board
GPS_PPS: U8.3 (TIMEPULSE); also elsewhere on the board
GPS_RESET: U8.11 (RESET); also elsewhere on the board
GPS_VBACKUP: U8.12 (V_BAKP); also elsewhere on the board
unnamed: LFP811.2, U8.19 (VCC_RF)

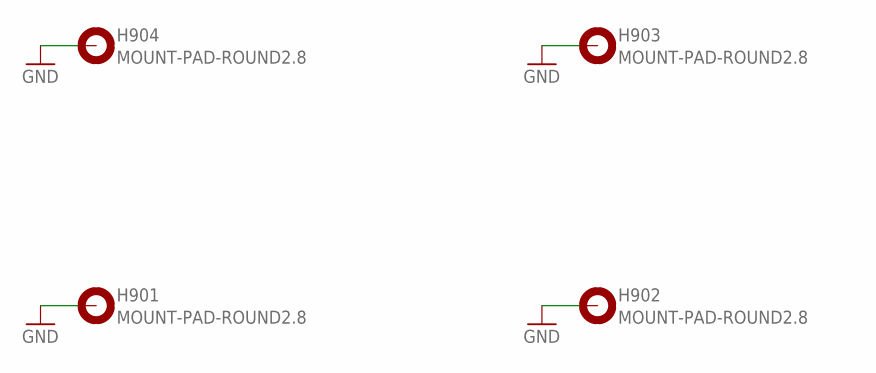
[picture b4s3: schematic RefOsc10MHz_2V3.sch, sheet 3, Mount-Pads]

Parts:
H901, H902, H903, H904: MOUNT-PAD-ROUND2.8; 2,8-PAD

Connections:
GND: H901.B2,8, H902.B2,8, H903.B2,8, H904.B2,8; also elsewhere on the board
